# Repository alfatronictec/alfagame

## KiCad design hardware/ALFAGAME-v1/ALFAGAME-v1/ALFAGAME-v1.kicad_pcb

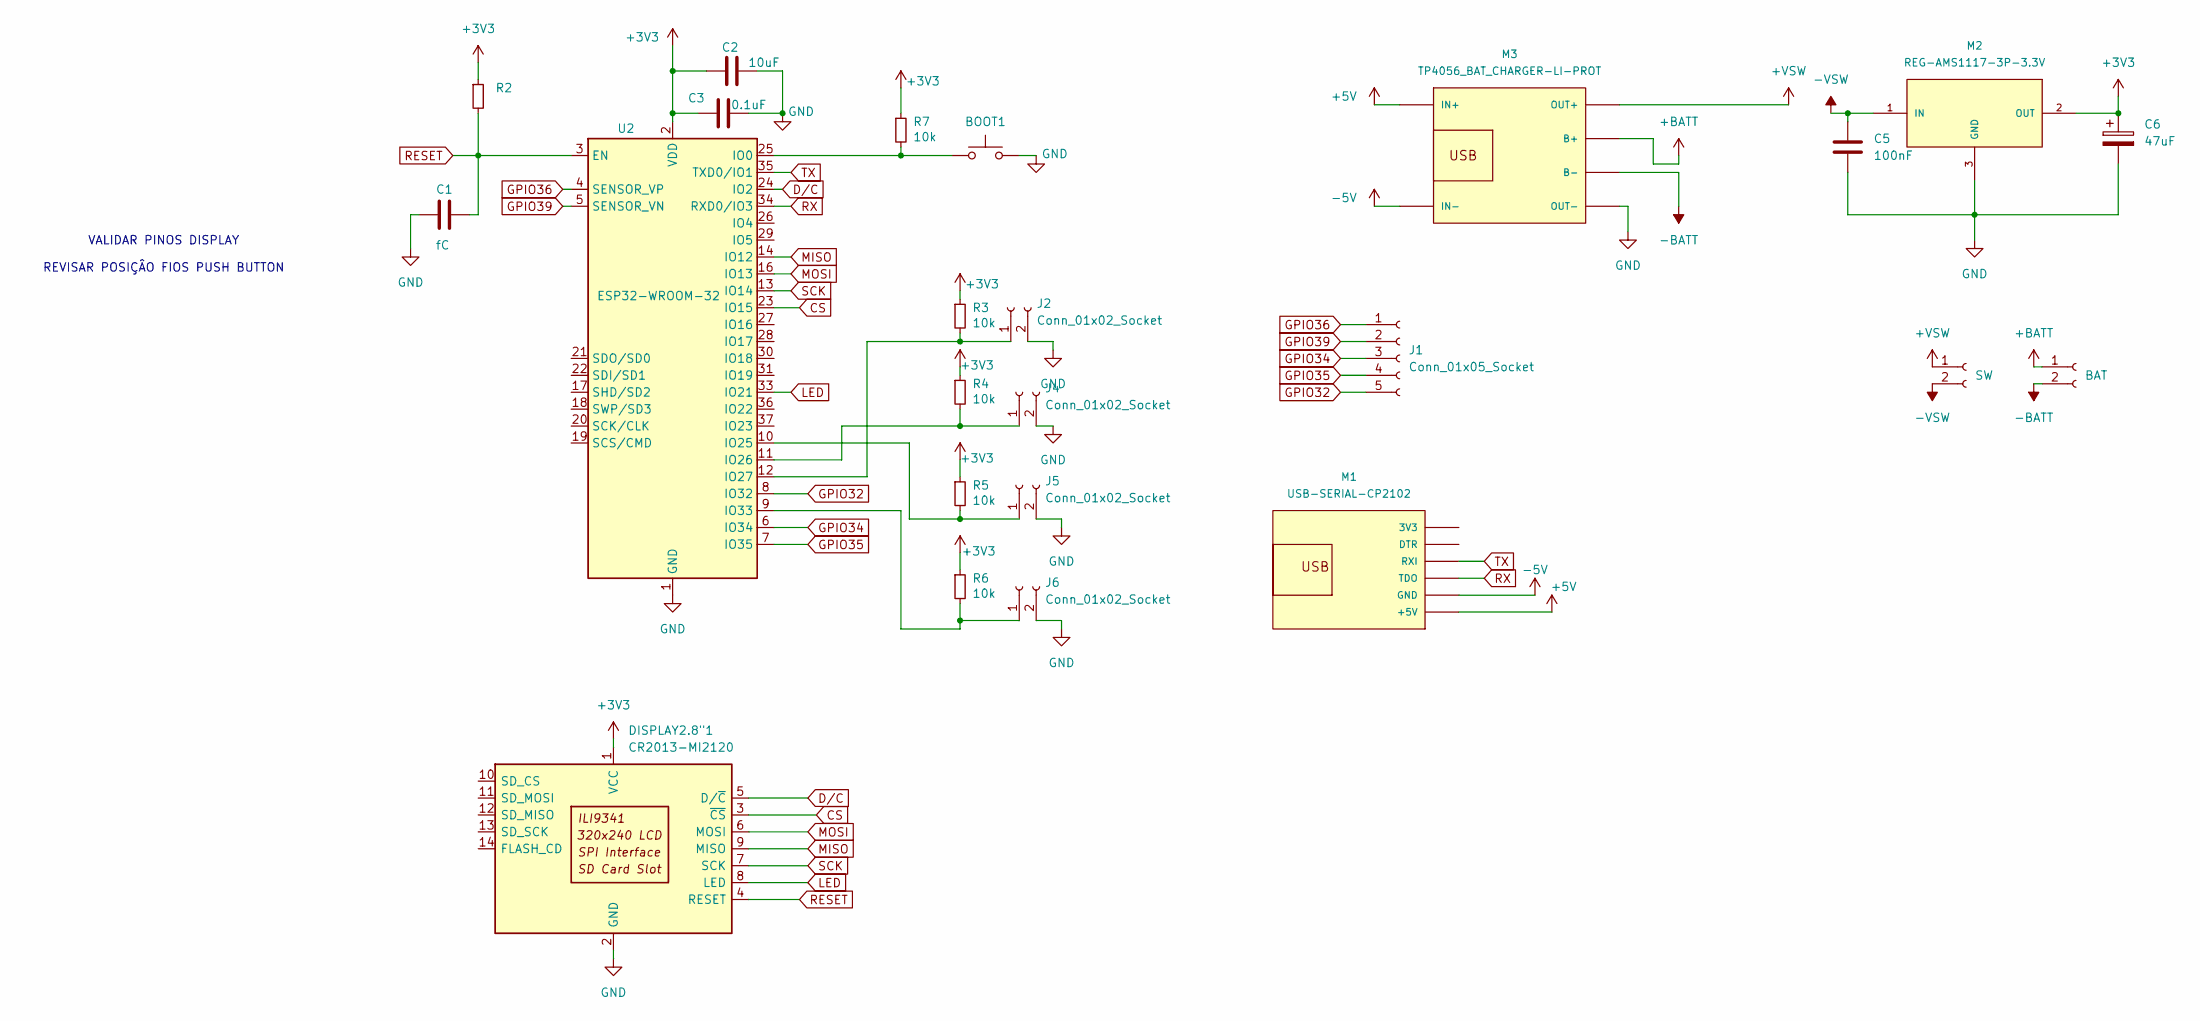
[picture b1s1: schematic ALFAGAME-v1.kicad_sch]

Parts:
BAT1: BAT; PinHeader_1x02_P2.54mm_Vertical
BOOT1: SW_Push; SW_PUSH_6mm_H13mm
C1: fC; C_1210_3225Metric
C2: 10uF; C_1210_3225Metric
C3: 0.1uF; C_1210_3225Metric
C5: 100nF; C_1210_3225Metric
C6: 47uF; CP_Radial_D5.0mm_P2.50mm
DISPLAY2.8"1: CR2013-MI2120
J1: Conn_01x05_Socket; PinHeader_1x05_P2.54mm_Vertical
J2, J4, J5, J6: Conn_01x02_Socket; PinHeader_1x02_P2.54mm_Vertical
M1: USB-SERIAL-CP2102
M2: REG-AMS1117-3P-3.3V; REG-AMS1117-3P#V
M3: TP4056_BAT_CHARGER-LI-PROT
R2: R_1206_3216Metric
R3, R4, R5, R6, R7: 10k; R_1206_3216Metric
SW1: SW; PinHeader_1x02_P2.54mm_Vertical
U2: ESP32-WROOM-32

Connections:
+3V3: C2.2, C3.2, C6.1, DISPLAY2.8"1.1 (VCC), M2.2 (OUT), R2.1, R3.1, R4.1, R5.1, R6.1, R7.1, U2.2 (VDD)
+5V: M1.6 (+5V), M3.IN+
+BATT: BAT1.1, M3.B+
+VSW: M3.OUT+, SW1.1
-5V: M1.5 (GND), M3.IN-
-BATT: BAT1.2, M3.B-
-VSW: C5.1, M2.1 (IN), SW1.2
CS: DISPLAY2.8"1.3 (~CS), U2.23 (IO15)
D/C: DISPLAY2.8"1.5 (D/~C), U2.24 (IO2)
GND: BOOT1.2, C1.2, C2.1, C3.1, C5.2, C6.2, DISPLAY2.8"1.2 (GND), J2.2, J4.2, J5.2, J6.2, M2.3 (GND), M3.OUT-, U2.1 (GND), U2.15 (GND), U2.38 (GND), U2.39 (GND)
GPIO32: J1.5, U2.8 (IO32)
GPIO34: J1.3, U2.6 (IO34)
GPIO35: J1.4, U2.7 (IO35)
GPIO36: J1.1, U2.4 (SENSOR_VP)
GPIO39: J1.2, U2.5 (SENSOR_VN)
LED: DISPLAY2.8"1.8 (LED), U2.33 (IO21)
MISO: DISPLAY2.8"1.9 (MISO), U2.14 (IO12)
MOSI: DISPLAY2.8"1.6 (MOSI), U2.16 (IO13)
unnamed: J2.1, R3.2, U2.12 (IO27)
unnamed: J4.1, R4.2, U2.11 (IO26)
unnamed: J5.1, R5.2, U2.10 (IO25)
unnamed: J6.1, R6.2, U2.9 (IO33)
unnamed: BOOT1.1, R7.2, U2.25 (IO0)
RESET: C1.1, DISPLAY2.8"1.4 (RESET), R2.2, U2.3 (EN)
RX: M1.4 (TDO), U2.34 (RXD0/IO3)
SCK: DISPLAY2.8"1.7 (SCK), U2.13 (IO14)
TX: M1.3 (RXI), U2.35 (TXD0/IO1)

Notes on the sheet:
VALIDAR PINOS DISPLAY REVISAR POSIÇÂO FIOS PUSH BUTTON

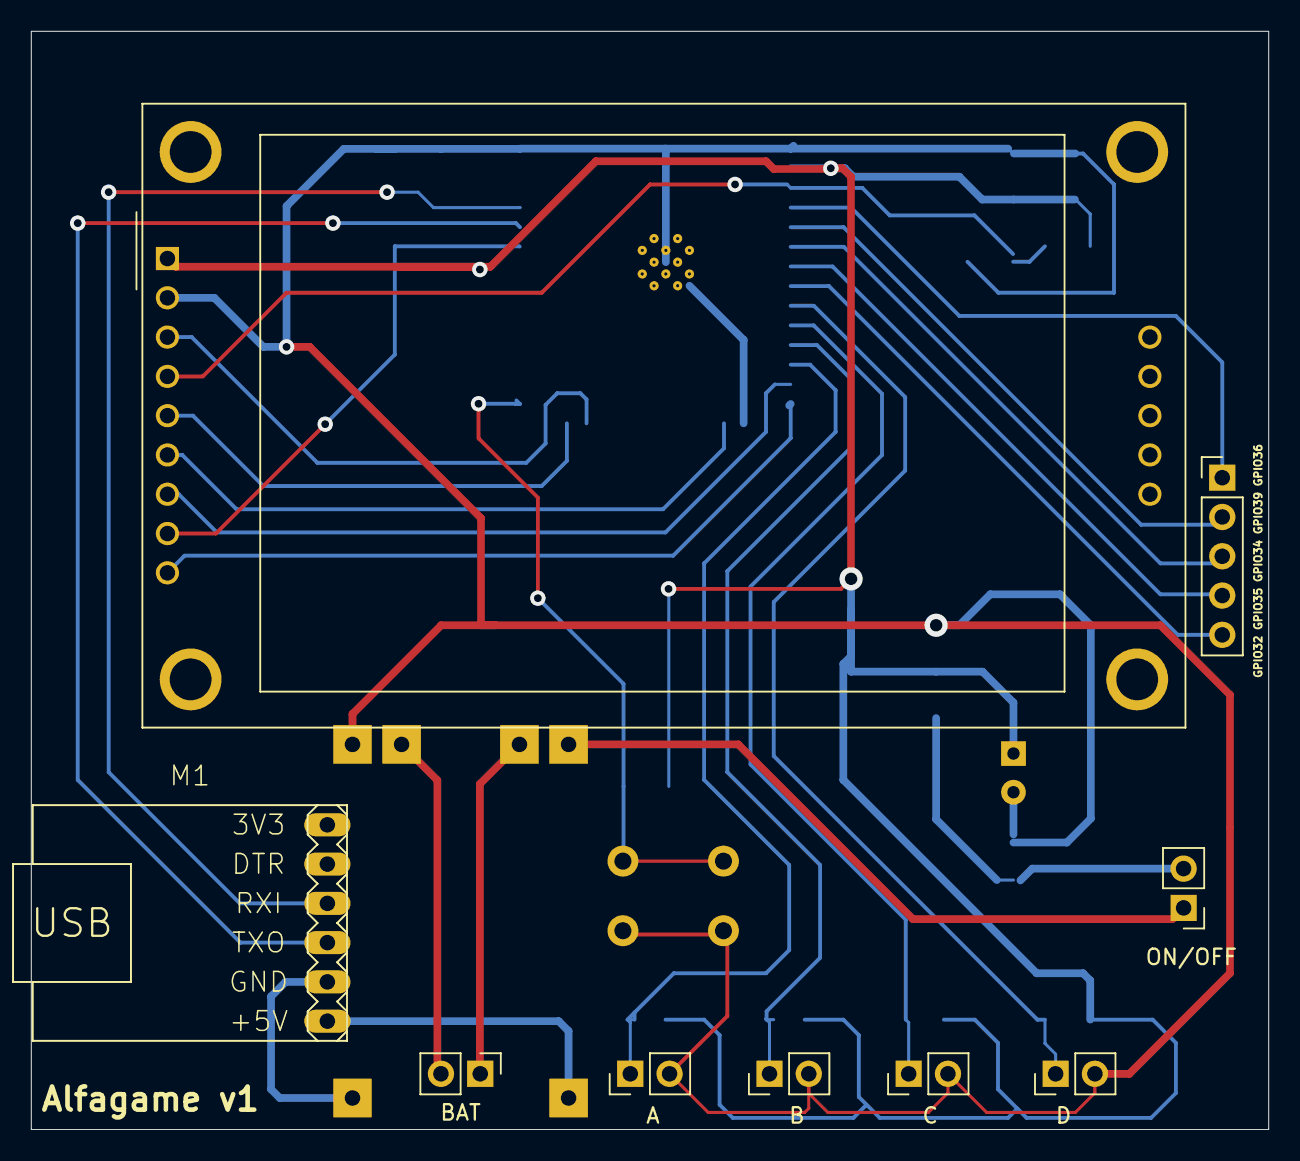
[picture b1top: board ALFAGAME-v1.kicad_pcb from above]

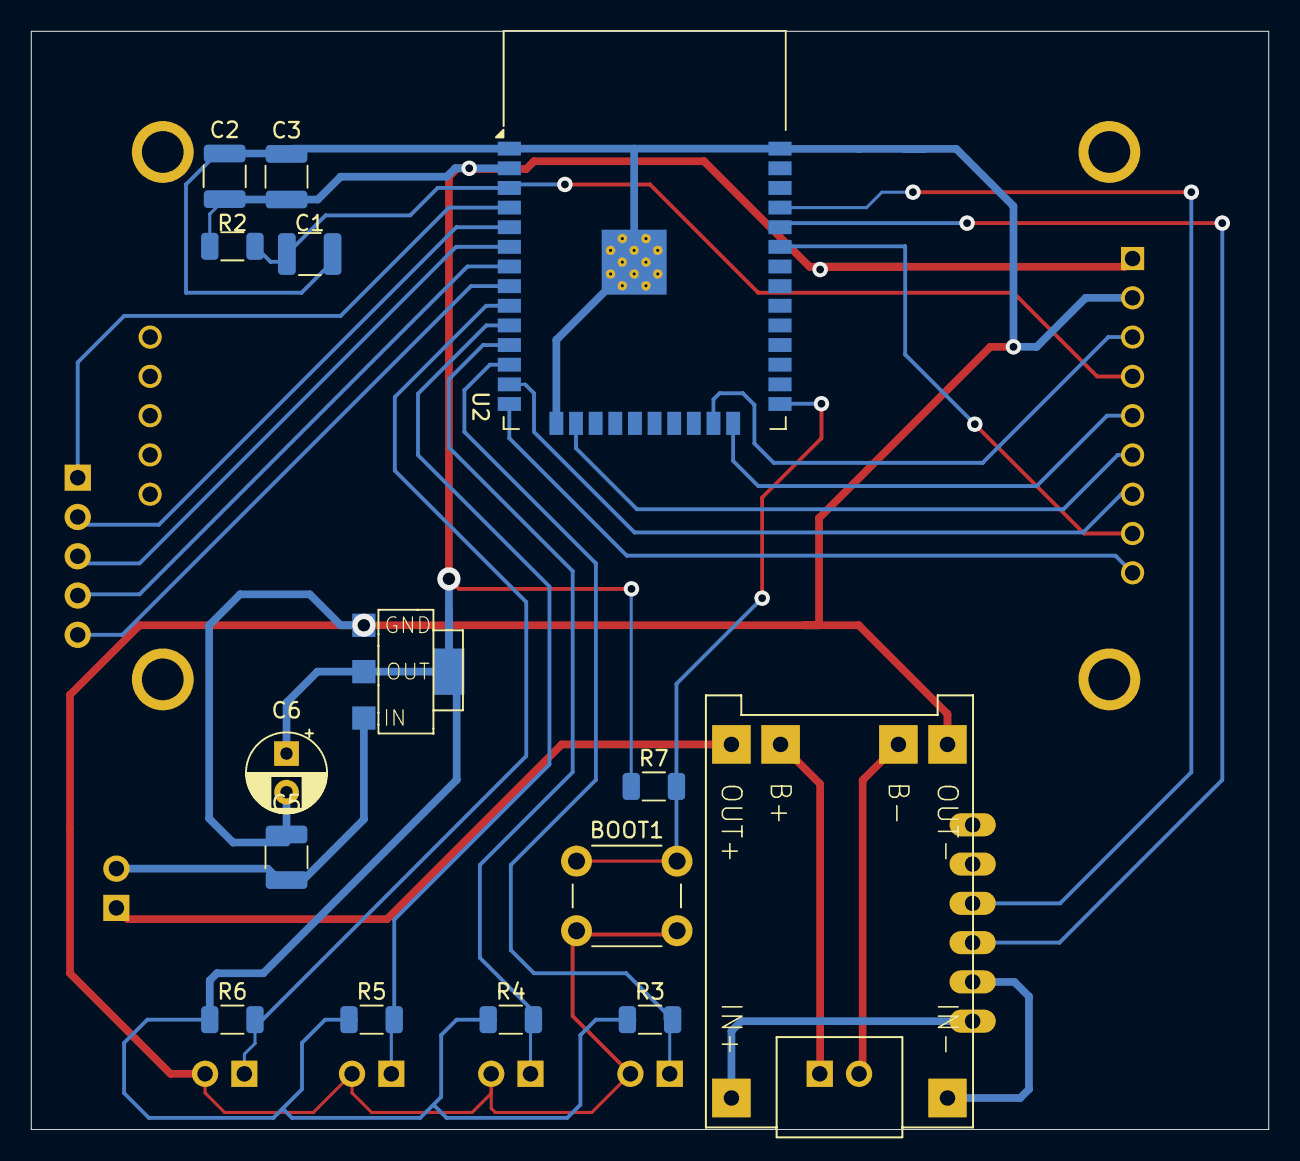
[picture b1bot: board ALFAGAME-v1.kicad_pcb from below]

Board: 2 copper layers, 80.0 x 71.0 mm, 24 parts (15 on the bottom side), 27 nets.

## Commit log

2026-02-15 Primeiro Commit
2026-02-15 Implementação de função de pergunta
2026-02-16 Continuação da Implantação das novas funções
